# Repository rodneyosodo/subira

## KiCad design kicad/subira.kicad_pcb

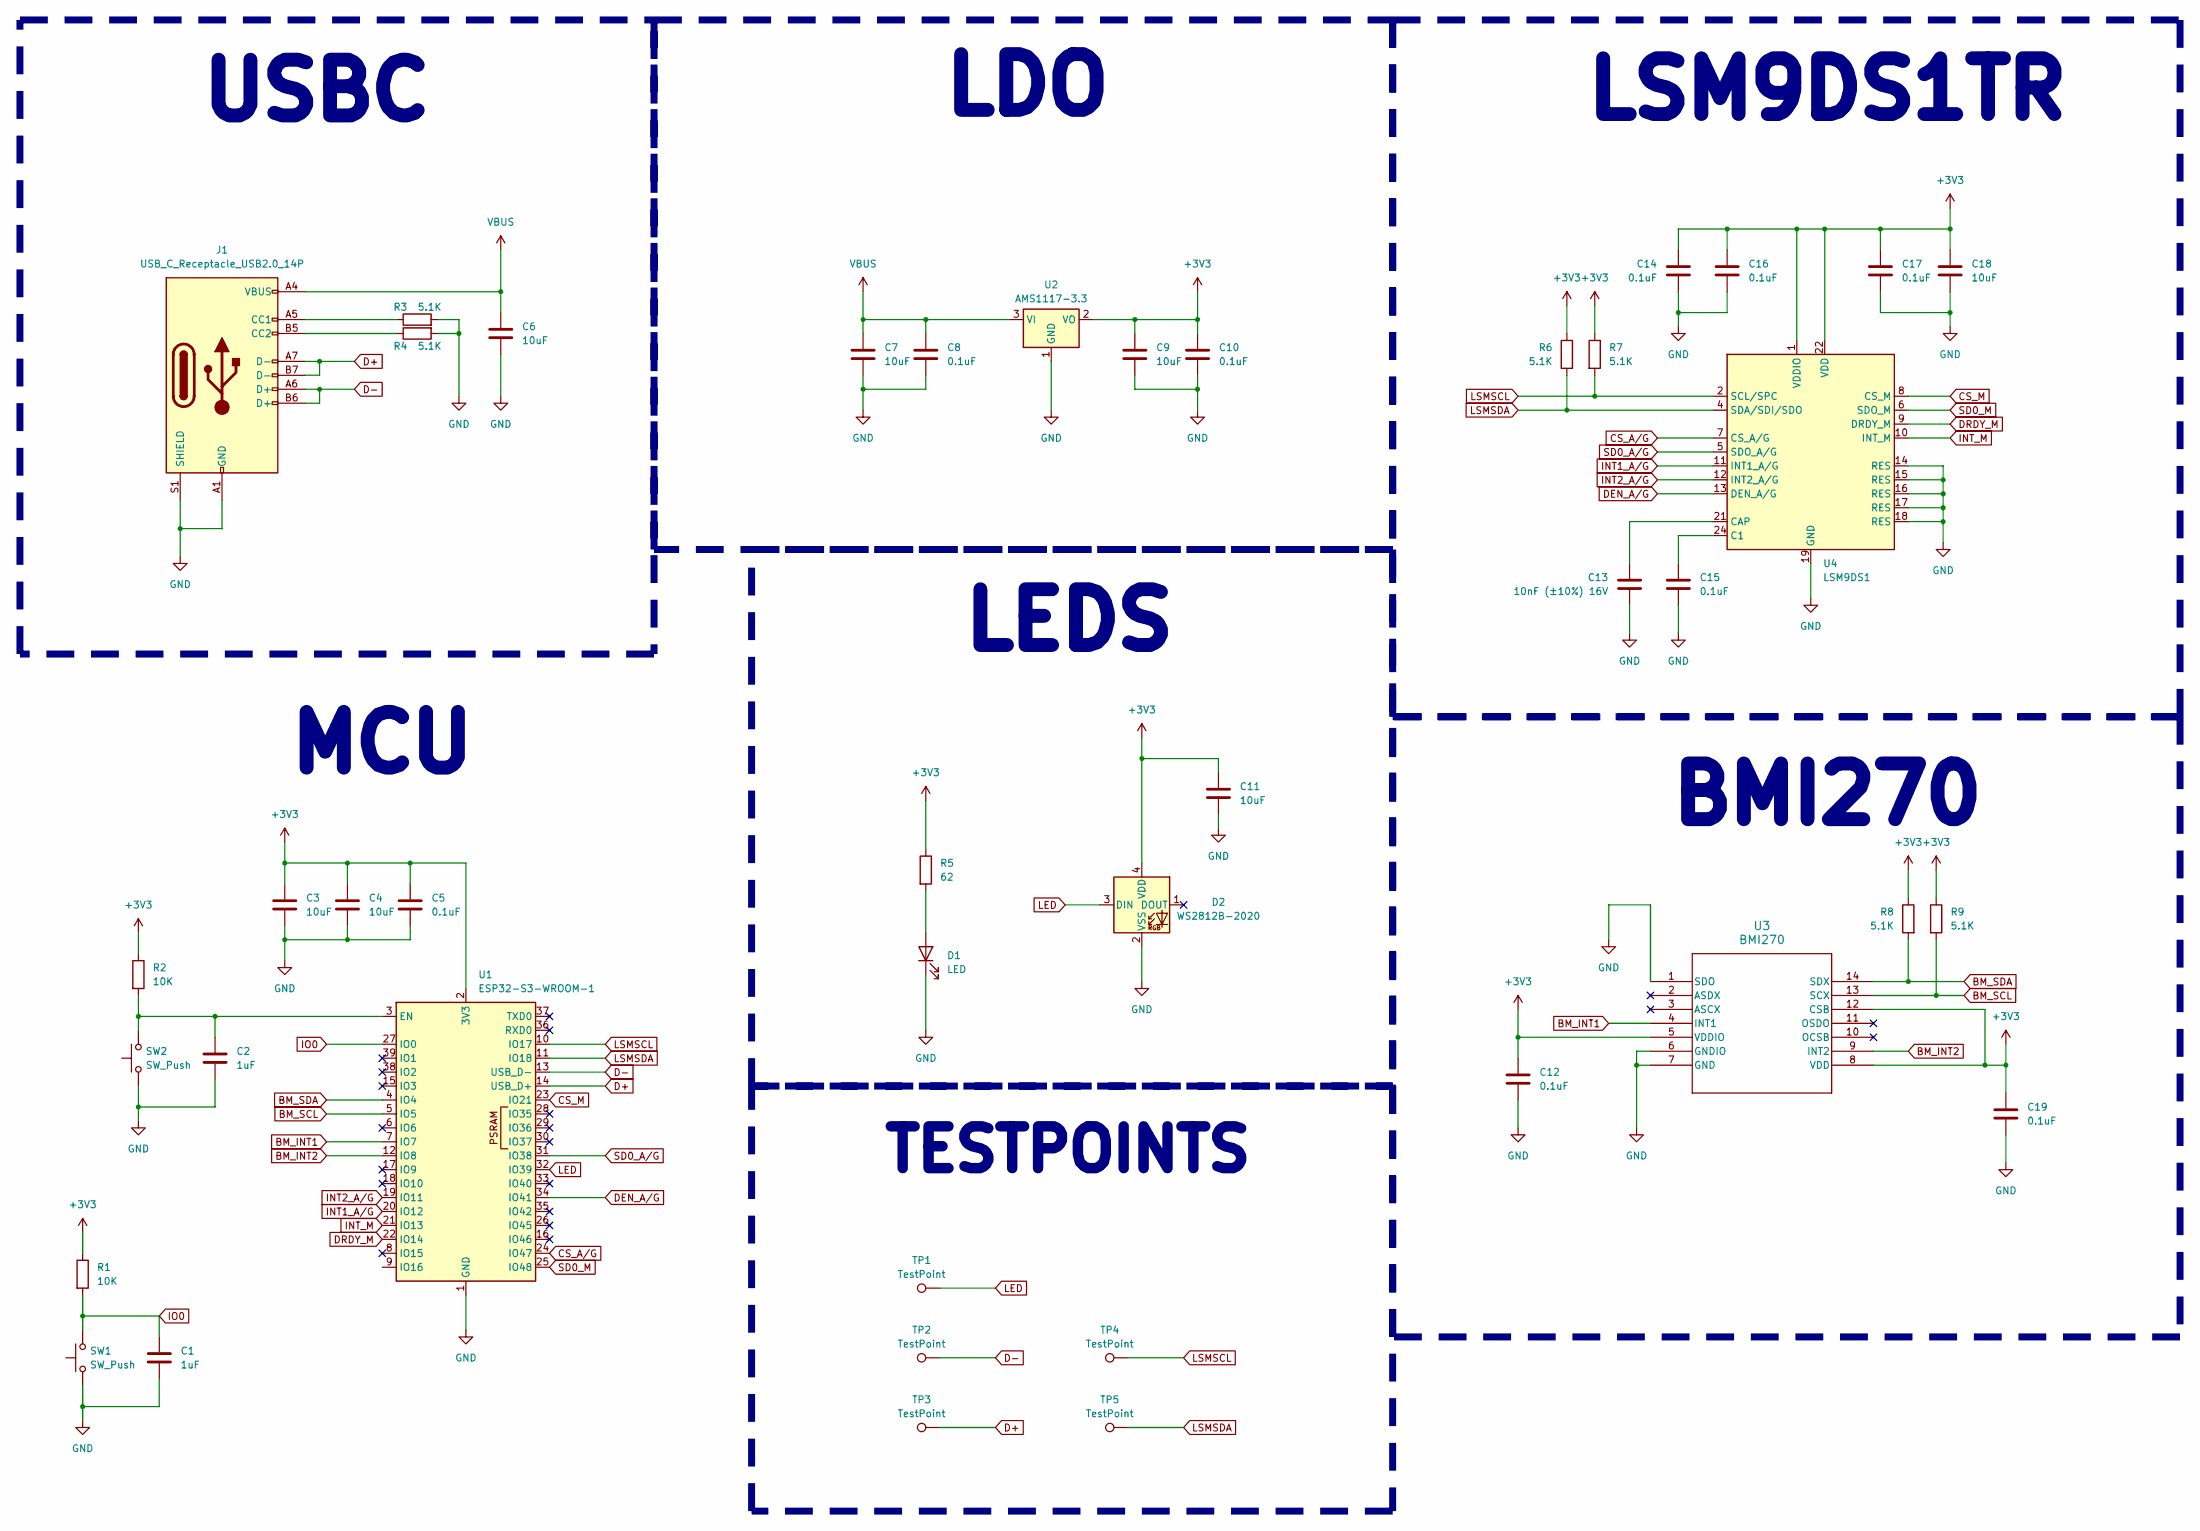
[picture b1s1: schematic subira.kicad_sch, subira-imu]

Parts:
C1, C2: 1uF; C_0603_1608Metric_Pad1.08x0.95mm_HandSolder; JLCPCB C15849
C3, C4, C6, C7, C9, C11, C18: 10uF; C_0603_1608Metric_Pad1.08x0.95mm_HandSolder; JLCPCB C96446
C5, C8, C10, C12, C14, C15, C16, C17, C19: 0.1uF; C_0603_1608Metric_Pad1.08x0.95mm_HandSolder; JLCPCB C88136
C13: 10nF (±10%) 16V; C_0603_1608Metric_Pad1.08x0.95mm_HandSolder; JLCPCB C57112
D1: LED; LED_0603_1608Metric; JLCPCB C2290
D2: WS2812B-2020; LED_WS2812B-2020_PLCC4_2.0x2.0mm; JLCPCB C965555
J1: USB_C_Receptacle_USB2.0_14P; USB_C_Receptacle_G-Switch_GT-USB-7010ASV; JLCPCB C393939
R1, R2: 10K; R_0603_1608Metric_Pad0.98x0.95mm_HandSolder; JLCPCB C25804
R3, R4, R6, R7, R8, R9: 5.1K; R_0603_1608Metric_Pad0.98x0.95mm_HandSolder; JLCPCB C23186
R5: 62; R_0603_1608Metric_Pad0.98x0.95mm_HandSolder; JLCPCB C23222
SW1, SW2: SW_Push; SW_Push_SPST_NO_Alps_SKRK; JLCPCB C720477
TP1, TP2, TP3, TP4, TP5: TestPoint; TestPoint_Pad_D2.0mm
U1: ESP32-S3-WROOM-1; JLCPCB C2913197
U2: AMS1117-3.3; SOT-223-3_TabPin2; JLCPCB C6186
U3: BMI270; BMI270_BOS-M; JLCPCB C2836813
U4: LSM9DS1; LGA-24L_3x3.5mm_P0.43mm; JLCPCB C2655096

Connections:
+3V3: C3.1, C4.1, C5.1, C9.1, C10.1, C11.1, C12.1, C14.1, C16.1, C17.1, C18.1, C19.1, D2.4 (VDD), R1.1, R2.1, R5.1, R6.1, R7.1, R8.1, R9.1, U1.2 (3V3), U2.2 (VO), U3.5 (VDDIO), U3.8 (VDD), U3.12 (CSB), U4.1 (VDDIO), U4.3 (VDDIO), U4.22 (VDD), U4.23 (VDD)
BM_INT1: U1.7 (IO7), U3.4 (INT1)
BM_INT2: U1.12 (IO8), U3.9 (INT2)
BM_SCL: R9.2, U1.5 (IO5), U3.13 (SCX)
BM_SDA: R8.2, U1.4 (IO4), U3.14 (SDX)
CS_A/G: U1.24 (IO47), U4.7 (CS_A/G)
CS_M: U1.23 (IO21), U4.8 (CS_M)
D+: J1.A7 (D-), J1.B7 (D-), TP3.1, U1.14 (USB_D+)
D-: J1.A6 (D+), J1.B6 (D+), TP2.1, U1.13 (USB_D-)
DEN_A/G: U1.34 (IO41), U4.13 (DEN_A/G)
DRDY_M: U1.22 (IO14), U4.9 (DRDY_M)
GND: C1.2, C2.2, C3.2, C4.2, C5.2, C6.2, C7.2, C8.2, C9.2, C10.2, C11.2, C12.2, C13.2, C14.2, C15.2, C16.2, C17.2, C18.2, C19.2, D1.1 (K), D2.2 (VSS), J1.A1 (GND), J1.A12 (GND), J1.B1 (GND), J1.B12 (GND), J1.S1 (SHIELD), R3.2, R4.2, SW1.1, SW2.1, U1.1 (GND), U1.40 (GND), U1.41 (GND), U2.1 (GND), U3.1 (SDO), U3.6 (GNDIO), U3.7 (GND), U4.14 (RES), U4.15 (RES), U4.16 (RES), U4.17 (RES), U4.18 (RES), U4.19 (GND), U4.20 (GND)
INT1_A/G: U1.20 (IO12), U4.11 (INT1_A/G)
INT2_A/G: U1.19 (IO11), U4.12 (INT2_A/G)
INT_M: U1.21 (IO13), U4.10 (INT_M)
IO0: C1.1, R1.2, SW1.2, U1.27 (IO0)
LED: D2.3 (DIN), TP1.1, U1.32 (IO39)
LSMSCL: R7.2, TP4.1, U1.10 (IO17), U4.2 (SCL/SPC)
LSMSDA: R6.2, TP5.1, U1.11 (IO18), U4.4 (SDA/SDI/SDO)
unnamed: D1.2 (A), R5.2
unnamed: J1.A5 (CC1), R3.1
unnamed: J1.B5 (CC2), R4.1
unnamed: C2.1, R2.2, SW2.2, U1.3 (EN)
unnamed: C15.1, U4.24 (C1)
unnamed: C13.1, U4.21 (CAP)
SD0_A/G: U1.31 (IO38), U4.5 (SDO_A/G)
SD0_M: U1.25 (IO48), U4.6 (SDO_M)
VBUS: C6.1, C7.1, C8.1, J1.A4 (VBUS), J1.A9 (VBUS), J1.B4 (VBUS), J1.B9 (VBUS), U2.3 (VI)

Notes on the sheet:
LSM9DS1TR
MCU
TESTPOINTS
BMI270
LDO
LEDS
USBC

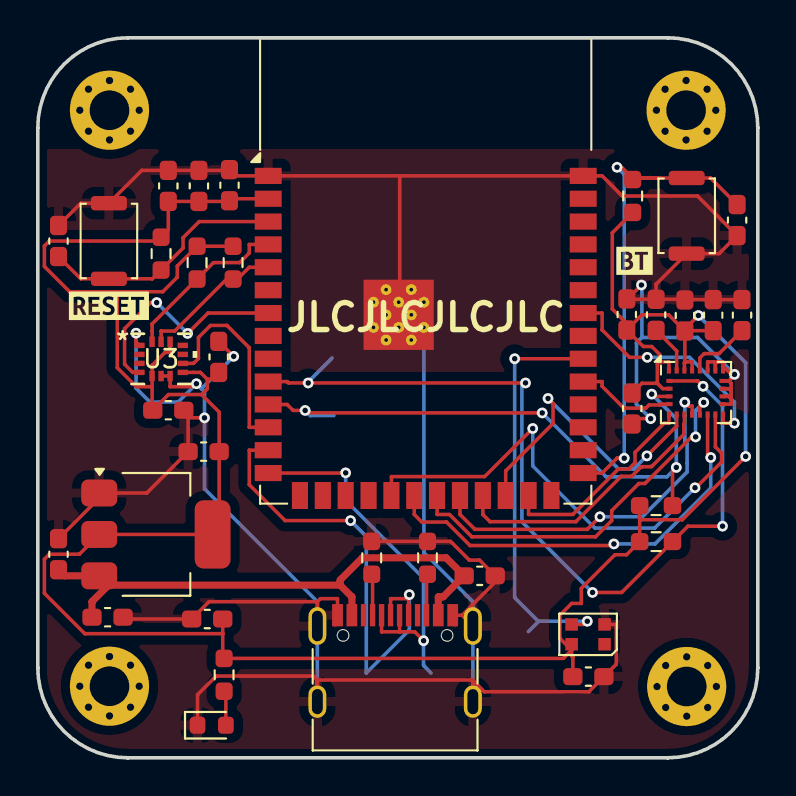
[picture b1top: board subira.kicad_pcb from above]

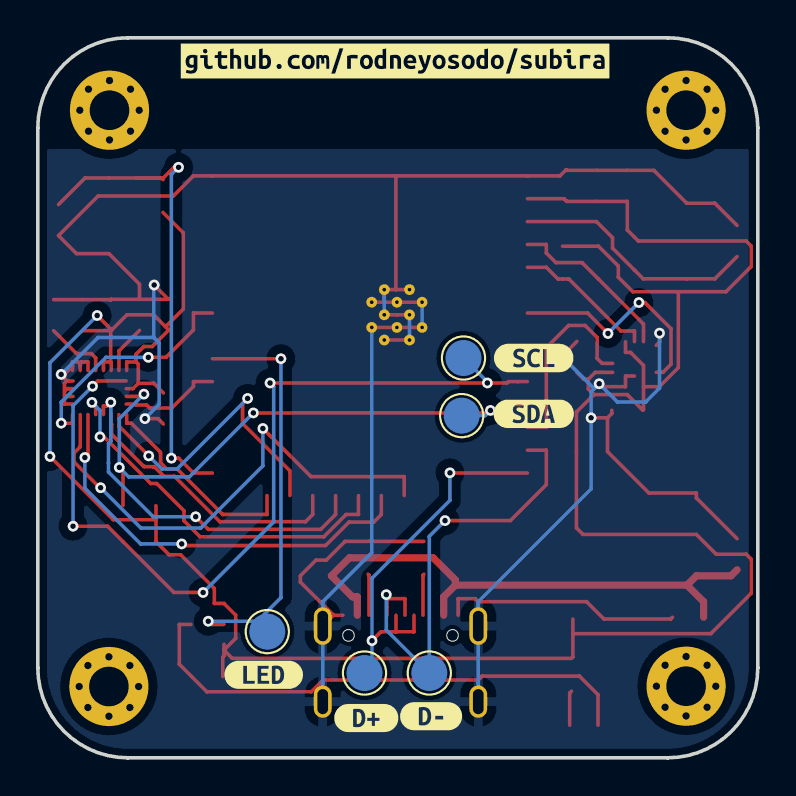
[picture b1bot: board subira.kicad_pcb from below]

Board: 2 copper layers, 40.0 x 40.0 mm, 54 parts (11 on the bottom side), 28 nets.

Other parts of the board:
REF1, REF2, REF3, REF4: MountingHole_2.2mm_M2_Pad_Via
kibuzzard-67E8F709: G***; kibuzzard-67E8F709
kibuzzard-67E8F774: G***; kibuzzard-67E8F774
kibuzzard-67E73E58: G***; kibuzzard-67E73E58
kibuzzard-67E73E61: G***; kibuzzard-67E73E61
kibuzzard-67E73E95: G***; kibuzzard-67E73E95
kibuzzard-67E73EA2: G***; kibuzzard-67E73EA2
kibuzzard-67E73EAE: G***; kibuzzard-67E73EAE
kibuzzard-67E73F75: G***; kibuzzard-67E73F75

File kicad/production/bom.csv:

"Reference","Value","Footprint","Qty","JLCPCB"
"C1,C2","1uF","Capacitor_SMD:C_0603_1608Metric_Pad1.08x0.95mm_HandSolder","2","C15849"
"C3,C4,C6,C7,C9,C11,C18","10uF","Capacitor_SMD:C_0603_1608Metric_Pad1.08x0.95mm_HandSolder","7","C96446"
"C5,C8,C10,C12,C14,C15,C16,C17,C19","0.1uF","Capacitor_SMD:C_0603_1608Metric_Pad1.08x0.95mm_HandSolder","9","C88136"
"C13","10nF (±10%) 16V","Capacitor_SMD:C_0603_1608Metric_Pad1.08x0.95mm_HandSolder","1","C57112"
"D1","LED","LED_SMD:LED_0603_1608Metric","1","C2290"
"D2","WS2812B-2020","LED_SMD:LED_WS2812B-2020_PLCC4_2.0x2.0mm","1","C965555"
"J1","USB_C_Receptacle_USB2.0_14P","Connector_USB:USB_C_Receptacle_G-Switch_GT-USB-7010ASV","1","C393939"
"R1,R2","10K","Resistor_SMD:R_0603_1608Metric_Pad0.98x0.95mm_HandSolder","2","C25804"
"R3,R4,R6,R7,R8,R9","5.1K","Resistor_SMD:R_0603_1608Metric_Pad0.98x0.95mm_HandSolder","6","C23186"
"R5","62","Resistor_SMD:R_0603_1608Metric_Pad0.98x0.95mm_HandSolder","1","C23222"
"SW1,SW2","SW_Push","Button_Switch_SMD:SW_Push_SPST_NO_Alps_SKRK","2","C720477"
"U1","ESP32-S3-WROOM-1","RF_Module:ESP32-S3-WROOM-1","1","C2913197"
"U2","AMS1117-3.3","Package_TO_SOT_SMD:SOT-223-3_TabPin2","1","C6186"
"U3","BMI270","modules:BMI270_BOS-M","1","C2836813"
"U4","LSM9DS1","Package_LGA:LGA-24L_3x3.5mm_P0.43mm","1","C2655096"

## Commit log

2025-03-29 feat(kicad): Add schematic and PCB files for productions
2025-03-29 fix: enable usb boot option
    Fixes https://github.com/rodneyosodo/subira/issues/2
    Fixes https://github.com/rodneyosodo/subira/issues/1
2025-03-30 fix: add labels to RST and BOOT buttons
2025-04-06 fix(schematic): add 5.1K pull up resistors
